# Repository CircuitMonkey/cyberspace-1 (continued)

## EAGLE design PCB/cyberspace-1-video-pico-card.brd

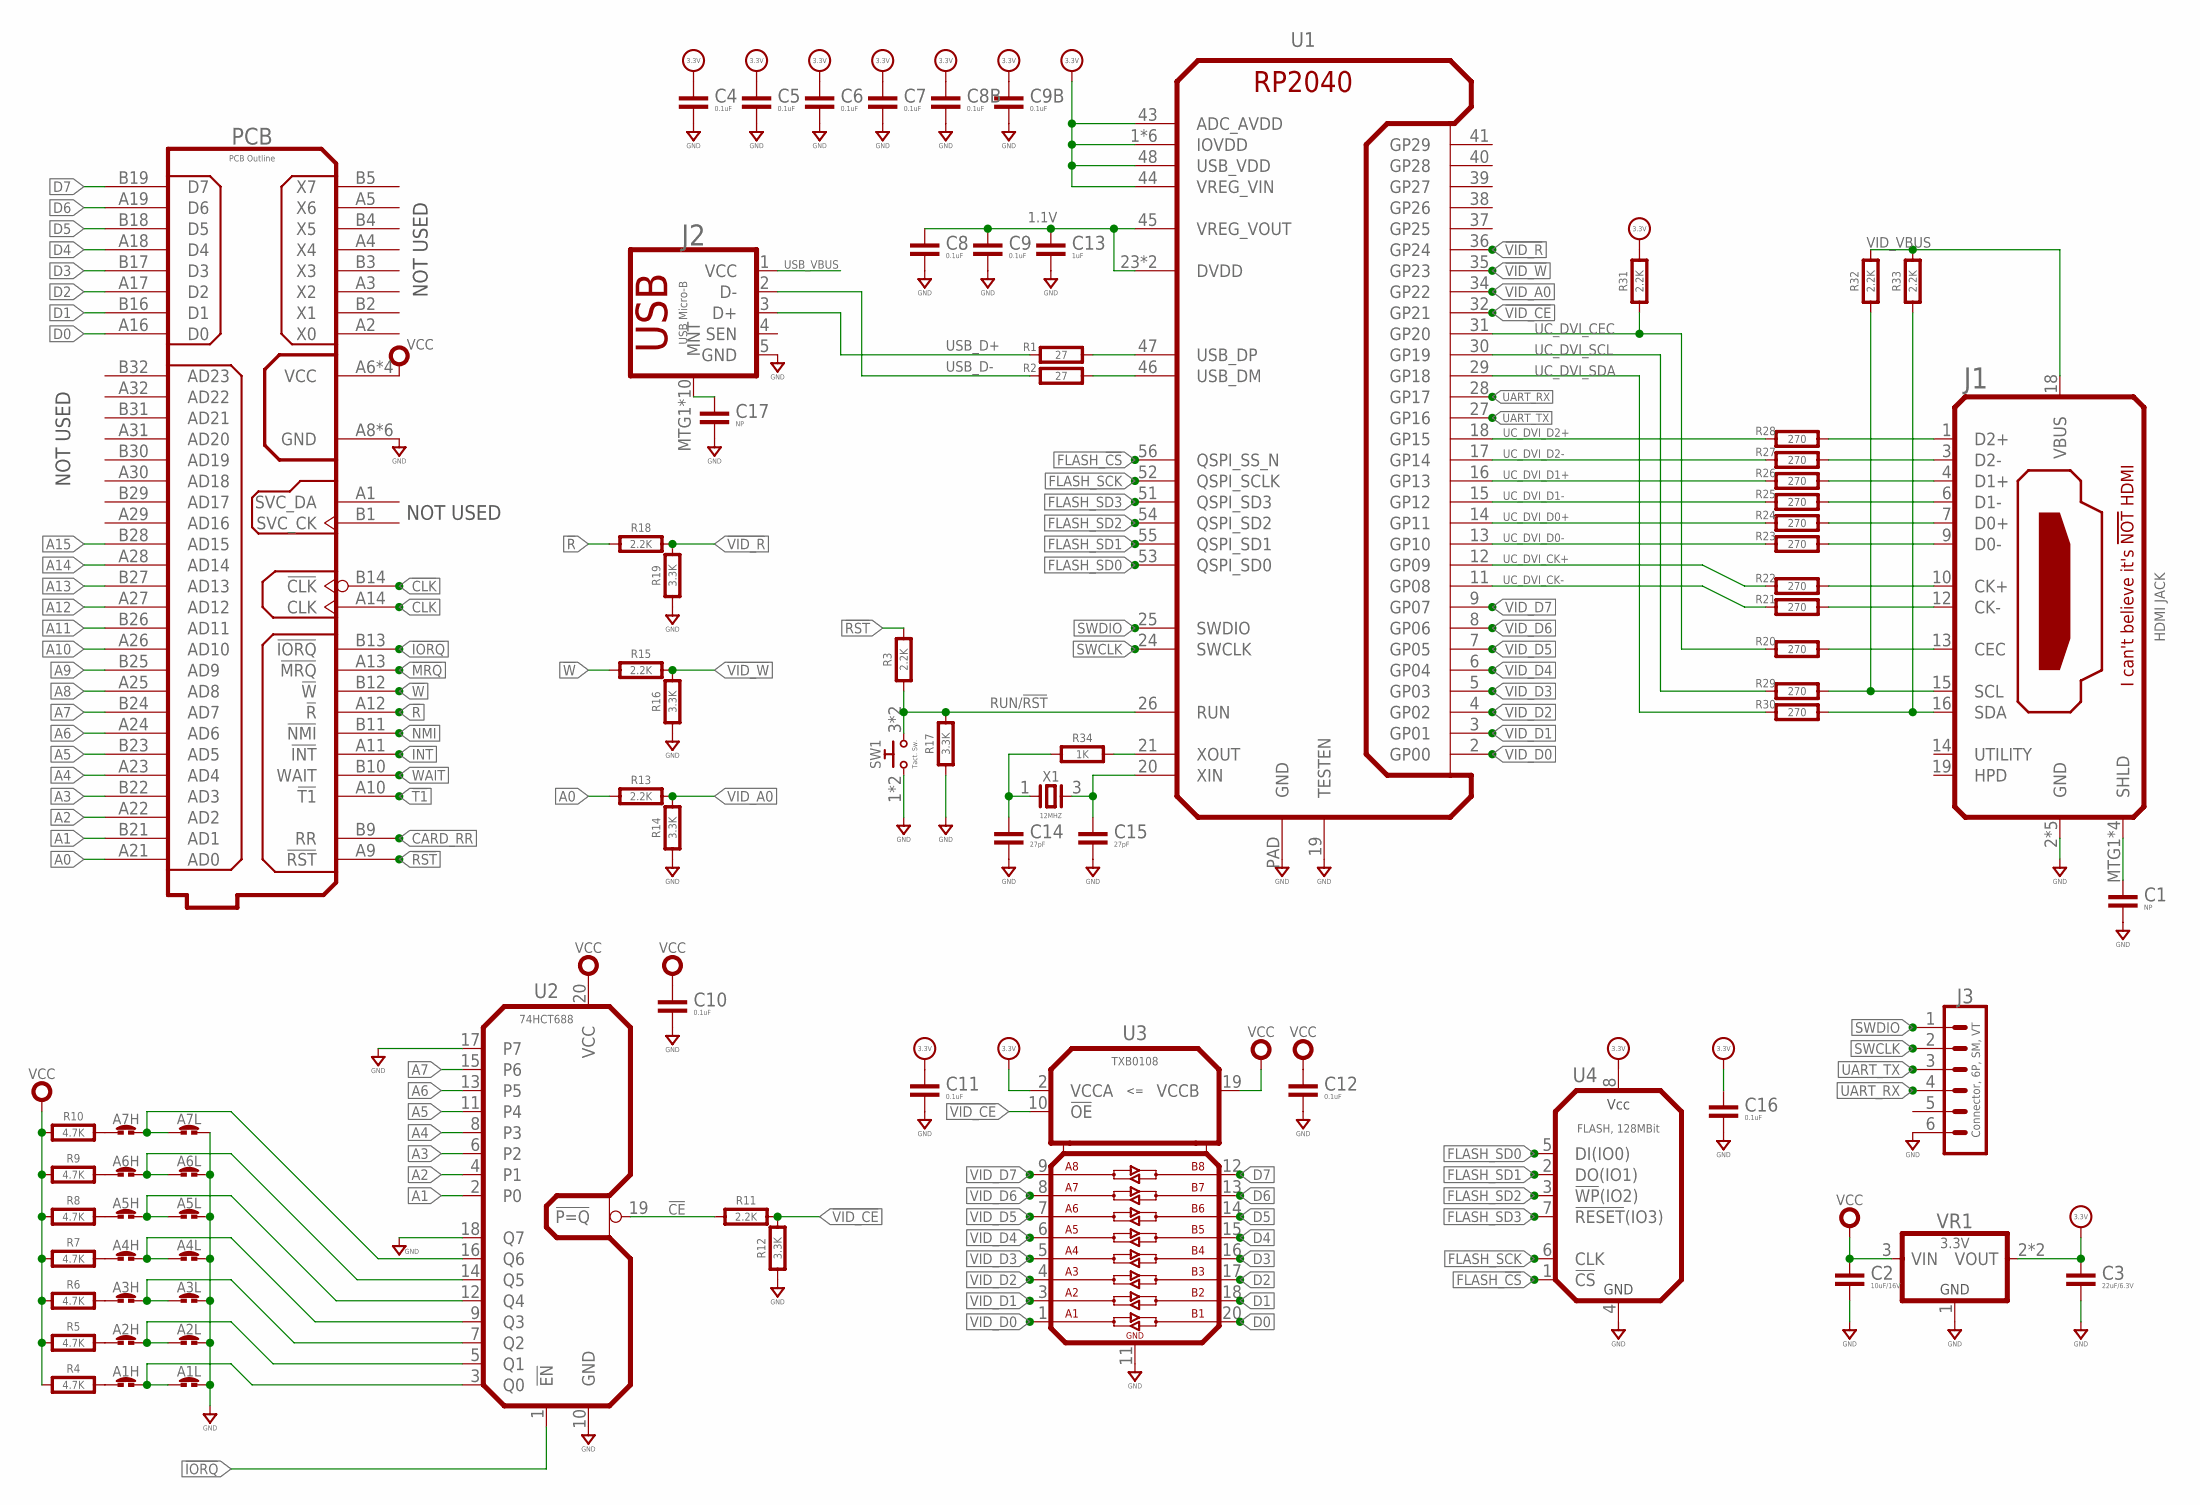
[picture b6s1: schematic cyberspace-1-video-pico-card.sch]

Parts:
A1H, A1L, A2H, A2L, A3H, A3L, A4H, A4L, A5H, A5L, A6H, A6L, A7H, A7L: SOLDER_JUMPER-80MIL-RND; SOLDER_JUMP_80MIL_RND
C1, C17: NP; 0603-CAP
C2: 10uF/16V; 0805-CAP
C3: 22uF/6.3V; 0805-CAP
C4, C5, C6, C7, C8, C8B, C9, C9B, C10, C11, C12, C16: 0.1uF; 0603-CAP
C13: 1uF; 0603-CAP
C14, C15: 27pF; 0603-CAP
J1: HDMI JACK; JAE-DC1-HDMI
J2: USB Micro-B; JAE-DX4R005
J3: Connector, 6P, SM, VT; BM06B-SRSS-TB
PCB: PCB Outline; CYBERSPACE-CARD-TYPE-1A
R1, R2: 27; 0603-RES
R3, R11, R13, R15, R18, R31, R32, R33: 2.2K; 0603-RES
R4, R5, R6, R7, R8, R9, R10: 4.7K; 0603-RES
R12, R14, R16, R17, R19: 3.3K; 0603-RES
R20, R21, R22, R23, R24, R25, R26, R27, R28, R29, R30: 270; 0603-RES
R34: 1K; 0603-RES
SW1: Tact. Sw.; B3FS
U1: RP2040-QFN; QFN56-7X7
U2: 74HCT688; TSSOP20
U3: TXB0108; TSSOP20
U4: FLASH, 128MBit; SOP08
VR1: 3.3V; SOT-223
X1: 12MHZ; 32X25

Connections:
1.1V: C8.1, C9.1, C13.1, U1.23 (DVDD), U1.45 (VREG_VOUT), U1.50 (DVDD)
!CE: R11.1, U2.19 (!P=Q)
!CLK: PCB.B14 (!CLK)
!INT: PCB.A11 (!INT)
!IORQ: PCB.B13 (!IORQ), U2.1 (!EN)
!MRQ: PCB.A13 (!MRQ)
!NMI: PCB.B11 (!NMI)
!R: PCB.A12 (!R), R18.1
!RST: PCB.A9 (!RST), R3.2
!T1: PCB.A10 (!T1)
!VID_CE: R11.2, R12.2, U1.32 (GP21), U3.10 (!OE)
!VID_R: R18.2, R19.2, U1.36 (GP24)
!VID_W: R15.2, R16.2, U1.35 (GP23)
!W: PCB.B12 (!W), R15.1
+3.3V: C3.1, C4.1, C5.1, C6.1, C7.1, C8B.1, C9B.1, C11.1, C16.1, R31.2, U1.1 (IOVDD), U1.10 (IOVDD), U1.22 (IOVDD), U1.33 (IOVDD), U1.42 (IOVDD), U1.43 (ADC_AVDD), U1.44 (VREG_VIN), U1.48 (USB_VDD), U1.49 (IOVDD), U3.2 (VCCA), U4.8 (VCC), VR1.2 (VOUT), VR1.TAB (VOUT)
A0: PCB.A21 (AD0), R13.1
A1: PCB.B21 (AD1), U2.2 (P0)
A2: PCB.A22 (AD2), U2.4 (P1)
A3: PCB.B22 (AD3), U2.6 (P2)
A4: PCB.A23 (AD4), U2.8 (P3)
A5: PCB.B23 (AD5), U2.11 (P4)
A6: PCB.A24 (AD6), U2.13 (P5)
A7: PCB.B24 (AD7), U2.15 (P6)
A8: PCB.A25 (AD8)
A9: PCB.B25 (AD9)
A10: PCB.A26 (AD10)
A11: PCB.B26 (AD11)
A12: PCB.A27 (AD12)
A13: PCB.B27 (AD13)
A14: PCB.A28 (AD14)
A15: PCB.B28 (AD15)
CARD_RR: PCB.B9 (RR)
CLK: PCB.A14 (CLK)
D0: PCB.A16 (D0), U3.20 (B1)
D1: PCB.B16 (D1), U3.18 (B2)
D2: PCB.A17 (D2), U3.17 (B3)
D3: PCB.B17 (D3), U3.16 (B4)
D4: PCB.A18 (D4), U3.15 (B5)
D5: PCB.B18 (D5), U3.14 (B6)
D6: PCB.A19 (D6), U3.13 (B7)
D7: PCB.B19 (D7), U3.12 (B8)
FLASH_!CS: U1.56 (QSPI_SS_N), U4.1 (!CS)
FLASH_SCK: U1.52 (QSPI_SCLK), U4.6 (CLK)
FLASH_SD0: U1.53 (QSPI_SD0), U4.5 (DI(IO0))
FLASH_SD1: U1.55 (QSPI_SD1), U4.2 (DO(IO1))
FLASH_SD2: U1.54 (QSPI_SD2), U4.3 (!WP!(IO2))
FLASH_SD3: U1.51 (QSPI_SD3), U4.7 (!RESET!(IO3))
GND: A1L.2, A2L.2, A3L.2, A4L.2, A5L.2, A6L.2, A7L.2, C1.2, C2.2, C3.2, C4.2, C5.2, C6.2, C7.2, C8.2, C8B.2, C9.2, C9B.2, C10.2, C11.2, C12.2, C13.2, C14.2, C15.2, C16.2, C17.2, J1.2 (GND), J1.5 (GND), J1.8 (GND), J1.11 (GND), J1.17 (GND), J2.5 (GND), J3.6, PCB.A8 (GND), PCB.A15 (GND), PCB.A20 (GND), PCB.B8 (GND), PCB.B15 (GND), PCB.B20 (GND), R12.1, R14.1, R16.1, R17.1, R19.1, SW1.1, SW1.2 (1), U1.19 (TESTEN), U1.PAD (GND), U2.10 (GND), U2.17 (P7), U3.11 (GND), U4.4 (GND), VR1.1 (GND)
unnamed: J1.13 (CEC), R20.2
unnamed: R1.2, U1.47 (USB_DP)
unnamed: R2.2, U1.46 (USB_DM)
unnamed: J1.12 (CK-), R21.2
unnamed: J1.10 (CK+), R22.2
unnamed: J1.9 (D0-), R23.2
unnamed: J1.7 (D0+), R24.2
unnamed: J1.6 (D1-), R25.2
unnamed: J1.4 (D1+), R26.2
unnamed: J1.3 (D2-), R27.2
unnamed: A1H.1, R4.2
unnamed: A1H.2, A1L.1, U2.3 (Q0)
unnamed: A2H.1, R5.2
unnamed: A2H.2, A2L.1, U2.5 (Q1)
unnamed: A3H.1, R6.2
unnamed: A3H.2, A3L.1, U2.7 (Q2)
unnamed: A4H.1, R7.2
unnamed: A4H.2, A4L.1, U2.9 (Q3)
unnamed: A5H.1, R8.2
unnamed: A5H.2, A5L.1, U2.12 (Q4)
unnamed: A6H.1, R9.2
unnamed: A6H.2, A6L.1, U2.14 (Q5)
unnamed: A7H.1, R10.2
unnamed: A7H.2, A7L.1, U2.16 (Q6)
unnamed: J1.1 (D2+), R28.2
unnamed: J1.15 (SCL), R29.2, R32.1
unnamed: J1.16 (SDA), R30.2, R33.1
unnamed: C1.1, J1.MTG1 (SHLD), J1.MTG2 (SHLD), J1.MTG3 (SHLD), J1.MTG4 (SHLD)
unnamed: R34.2, U1.21 (XOUT)
unnamed: C14.1, R34.1, X1.1
unnamed: C15.1, U1.20 (XIN), X1.3
unnamed: C17.1, J2.MTG1 (MNT), J2.MTG2 (MNT), J2.MTG3 (MNT), J2.MTG4 (MNT), J2.MTG5 (MNT), J2.MTG6 (MNT), J2.MTG7 (MNT), J2.MTG8 (MNT), J2.MTG9 (MNT), J2.MTG10 (MNT)
RUN/!RST: R3.1, R17.2, SW1.3 (2), SW1.4 (2), U1.26 (RUN)
SWCLK: J3.2, U1.24 (SWCLK)
SWDIO: J3.1, U1.25 (SWDIO)
UART_RX: J3.4, U1.28 (GP17)
UART_TX: J3.3, U1.27 (GP16)
UC_DVI_CEC: R20.1, R31.1, U1.31 (GP20)
UC_DVI_CK+: R22.1, U1.12 (GP09)
UC_DVI_CK-: R21.1, U1.11 (GP08)
UC_DVI_D0+: R24.1, U1.14 (GP11)
UC_DVI_D0-: R23.1, U1.13 (GP10)
UC_DVI_D1+: R26.1, U1.16 (GP13)
UC_DVI_D1-: R25.1, U1.15 (GP12)
UC_DVI_D2+: R28.1, U1.18 (GP15)
UC_DVI_D2-: R27.1, U1.17 (GP14)
UC_DVI_SCL: R29.1, U1.30 (GP19)
UC_DVI_SDA: R30.1, U1.29 (GP18)
USB_D+: J2.3 (D+), R1.1
USB_D-: J2.2 (D-), R2.1
USB_VBUS: J2.1 (VCC)
VCC: C2.1, C10.1, C12.1, PCB.A6 (VCC), PCB.A7 (VCC), PCB.B6 (VCC), PCB.B7 (VCC), R4.1, R5.1, R6.1, R7.1, R8.1, R9.1, R10.1, U2.20 (VCC), U3.19 (VCCB), VR1.3 (VIN)
VID_A0: R13.2, R14.2, U1.34 (GP22)
VID_D0: U1.2 (GP00), U3.1 (A1)
VID_D1: U1.3 (GP01), U3.3 (A2)
VID_D2: U1.4 (GP02), U3.4 (A3)
VID_D3: U1.5 (GP03), U3.5 (A4)
VID_D4: U1.6 (GP04), U3.6 (A5)
VID_D5: U1.7 (GP05), U3.7 (A6)
VID_D6: U1.8 (GP06), U3.8 (A7)
VID_D7: U1.9 (GP07), U3.9 (A8)
VID_VBUS: J1.18 (VBUS), R32.2, R33.2
WAIT: PCB.B10 (WAIT)

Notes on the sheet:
NOT USED

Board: 2 copper layers, 78 parts (0 on the bottom side), 94 nets, no tracks yet.

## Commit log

2023-11-16 Mid-November work-in-process checkpoint.
    All schematics complete. All board placement finished. Needs routing.
2023-11-22 Board routed. Needs tuning.
2023-11-25 Mainboard DRC passed. New stand-in logo.
2023-11-28 CPU PCB routed.
2023-12-06 Clock Card final?
2023-12-23 Tune mainboard routing.
2023-12-23 PCBs as FABed 12-2023
2024-01-12 Resistor missing value.
2024-01-12 BOM and some photos.
2024-01-21 Add clock card BOM.
2024-01-21 Update BOM
2024-01-21 Update README.md
    Added photos and release notes.
2024-01-22 WIP. Proposed clock fix in schematic.
2024-02-02 Routed RAM-ROM card. Almost there.
2024-02-04 New RamRom using flash chip.
2024-02-06 Add notes on edge connector.
2024-02-06 GitHub did something weird. All new files and no idea why.
2024-02-07 Create initial light show for Main Board
